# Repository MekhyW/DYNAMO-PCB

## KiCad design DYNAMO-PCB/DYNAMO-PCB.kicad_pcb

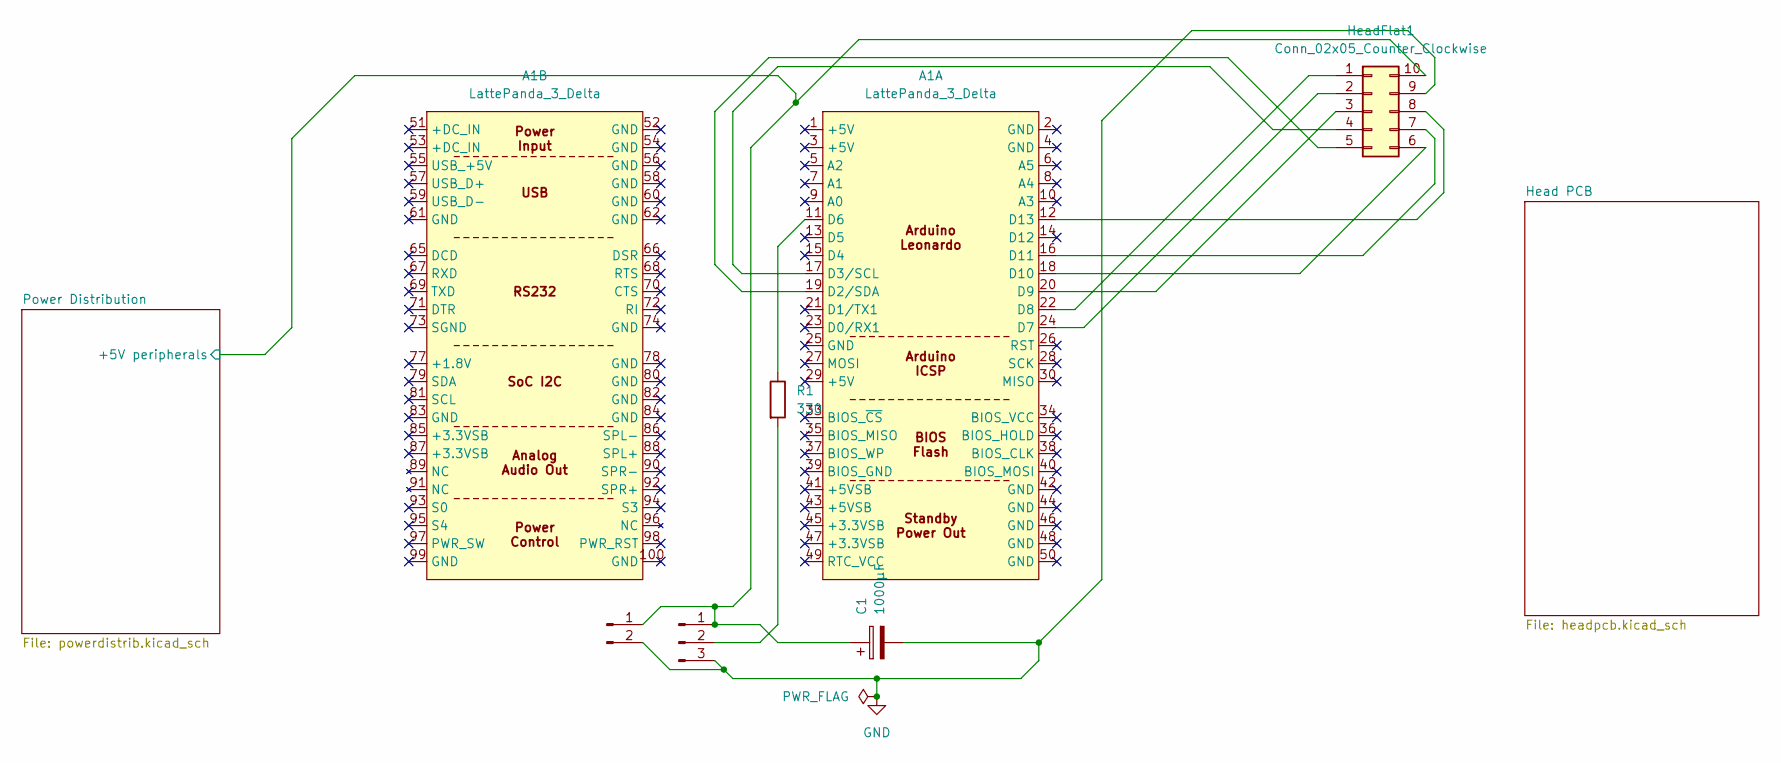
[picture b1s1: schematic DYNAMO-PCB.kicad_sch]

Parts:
A1: LattePanda_3_Delta
C1: 1000µF; CP_Radial_D10.0mm_P5.00mm
CentralFan1: Conn_01x02_Pin; PinHeader_1x02_P2.54mm_Vertical
CentralLEDs1: Conn_01x03_Pin; PinHeader_1x03_P2.54mm_Vertical
HeadFlat1: Conn_02x05_Counter_Clockwise; PinHeader_2x05_P2.54mm_Vertical
R1: 330; R_Axial_DIN0309_L9.0mm_D3.2mm_P12.70mm_Horizontal

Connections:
/Power Distribution/+5V peripherals: C1.1, CentralFan1.1, CentralLEDs1.1, HeadFlat1.10; also elsewhere on the board
GND: C1.2, CentralFan1.2, CentralLEDs1.3, HeadFlat1.9; also elsewhere on the board
unnamed: A1.19 (D2/SDA), HeadFlat1.5
unnamed: A1.17 (D3/SCL), HeadFlat1.4
unnamed: A1.11 (D6), R1.1
unnamed: A1.24 (D7), HeadFlat1.2
unnamed: A1.22 (D8), HeadFlat1.1
unnamed: A1.20 (D9), HeadFlat1.3
unnamed: A1.18 (D10), HeadFlat1.6
unnamed: A1.16 (D11), HeadFlat1.7
unnamed: A1.12 (D13), HeadFlat1.8
unnamed: CentralLEDs1.2, R1.2

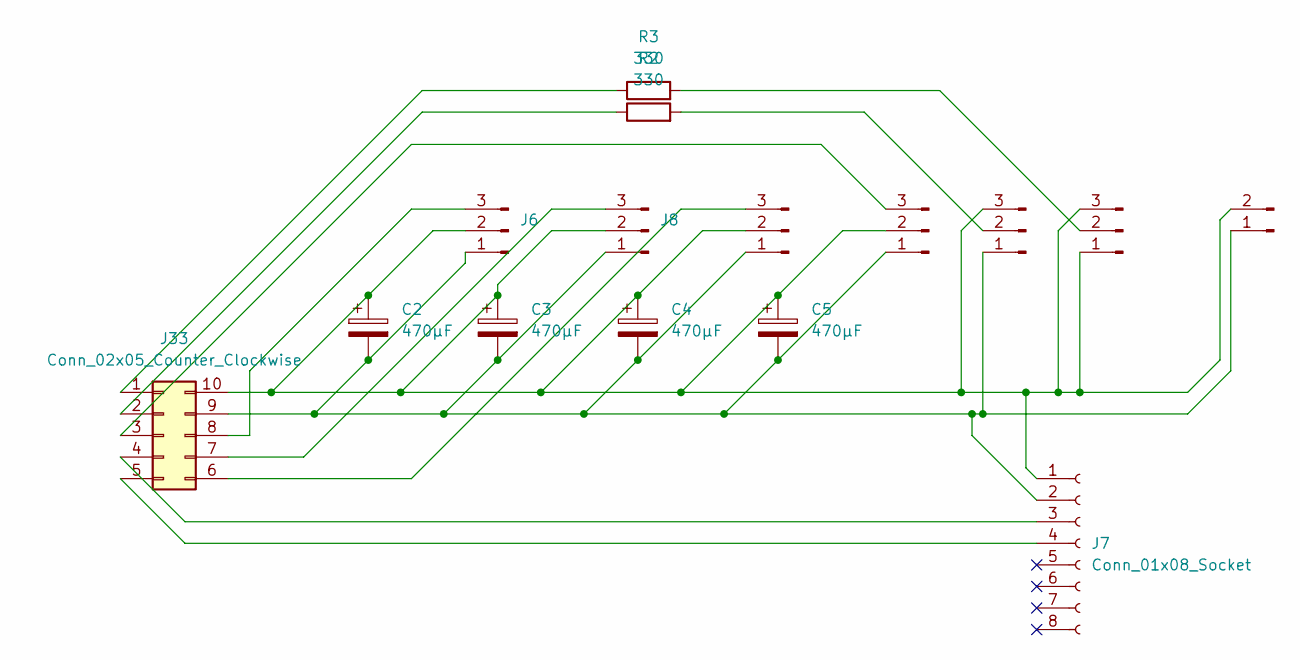
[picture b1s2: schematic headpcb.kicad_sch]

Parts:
C2, C3, C4, C5: 470µF; CP_Radial_D8.0mm_P3.50mm
J5: Conn_01x02_Pin; PinHeader_1x02_P2.54mm_Vertical
J6, J8, J9, J10, J11, J12: Conn_01x03_Pin; PinHeader_1x03_P2.54mm_Vertical
J7: Conn_01x08_Socket; PinSocket_1x08_P2.54mm_Horizontal
J33: Conn_02x05_Counter_Clockwise; PinHeader_2x05_P2.54mm_Vertical
R2, R3: 330; R_Axial_DIN0309_L9.0mm_D3.2mm_P12.70mm_Horizontal

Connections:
unnamed: C2.2, C3.2, C4.2, C5.2, J5.1, J6.1, J7.2, J8.1, J9.1, J10.1, J11.1, J33.9
unnamed: C2.1, C3.1, C4.1, C5.1, J5.2, J6.2, J7.1, J8.2, J9.2, J10.2, J11.3, J12.1, J12.3, J33.10
unnamed: J10.3, J33.3
unnamed: J11.2, R2.2
unnamed: J12.2, R3.2
unnamed: J33.1, R3.1
unnamed: J33.2, R2.1
unnamed: J7.3, J33.4
unnamed: J7.4, J33.5
unnamed: J9.3, J33.6
unnamed: J8.3, J33.7
unnamed: J6.3, J33.8

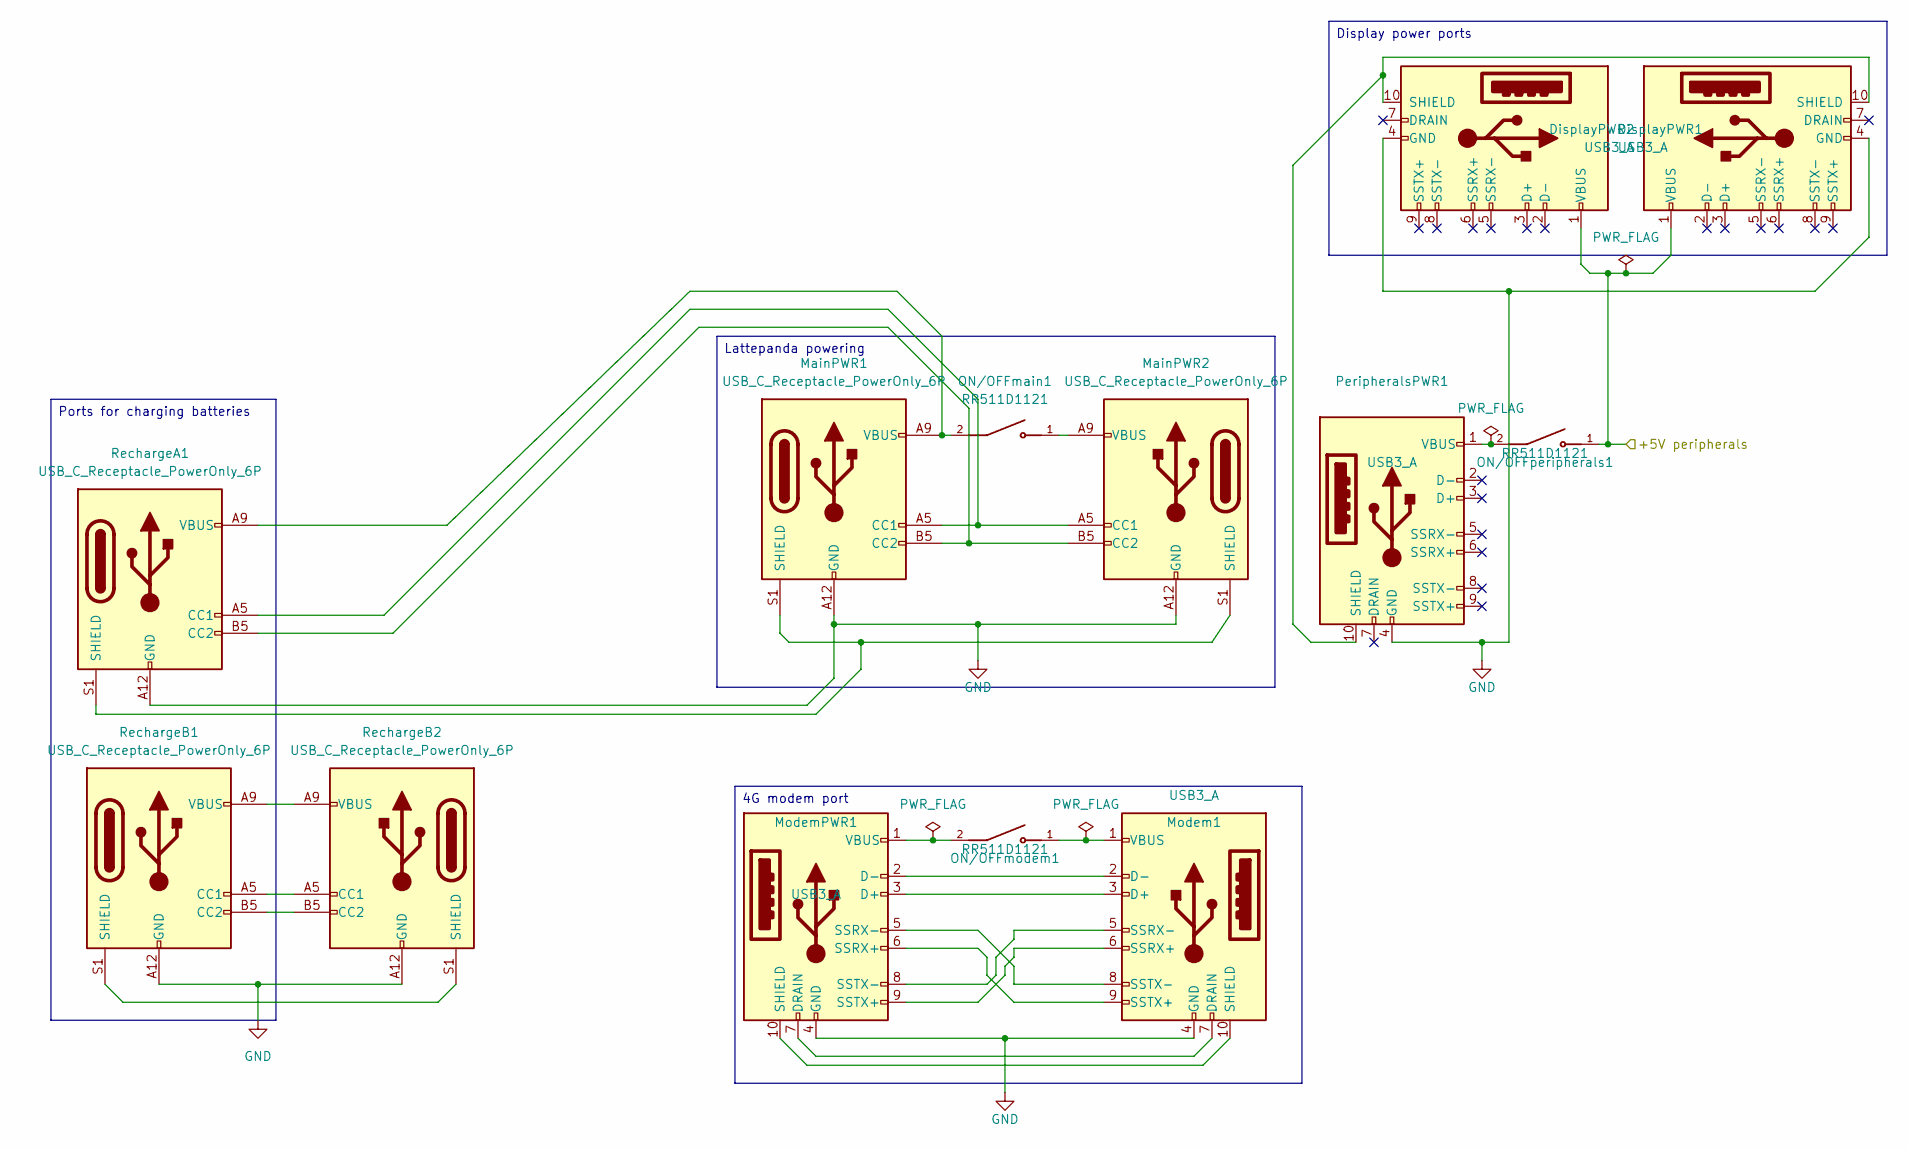
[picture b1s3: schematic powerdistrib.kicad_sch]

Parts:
DisplayPWR1, DisplayPWR2: USB3_A; 692122030100
MainPWR1, MainPWR2: USB_C_Receptacle_PowerOnly_6P; USB_C_Receptacle_GCT_USB4125-xx-x_6P_TopMnt_Horizontal
Modem1: USB3_A; 692122030100
ModemPWR1: USB3_A; 692122030100
ON/OFFmain1: RR511D1121; E-SWITCH_RR511D1121; PARTREV A
ON/OFFmodem1: RR511D1121; E-SWITCH_RR511D1121; PARTREV A
ON/OFFperipherals1: RR511D1121; E-SWITCH_RR511D1121; PARTREV A
PeripheralsPWR1: USB3_A; 692122030100
RechargeA1: USB_C_Receptacle_PowerOnly_6P; USB_C_Receptacle_GCT_USB4125-xx-x_6P_TopMnt_Horizontal
RechargeB1, RechargeB2: USB_C_Receptacle_PowerOnly_6P; USB_C_Receptacle_GCT_USB4125-xx-x_6P_TopMnt_Horizontal

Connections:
/Power Distribution/+5V peripherals: DisplayPWR1.1 (VBUS), DisplayPWR2.1 (VBUS), ON/OFFperipherals1.1; also elsewhere on the board
GND: DisplayPWR1.4 (GND), DisplayPWR2.4 (GND), MainPWR1.A12 (GND), MainPWR1.B12 (GND), MainPWR2.A12 (GND), MainPWR2.B12 (GND), Modem1.4 (GND), ModemPWR1.4 (GND), PeripheralsPWR1.4 (GND), RechargeA1.A12 (GND), RechargeA1.B12 (GND), RechargeB1.A12 (GND), RechargeB1.B12 (GND), RechargeB2.A12 (GND), RechargeB2.B12 (GND); also elsewhere on the board
unnamed: DisplayPWR1.10 (SHIELD), DisplayPWR2.10 (SHIELD), PeripheralsPWR1.10 (SHIELD)
unnamed: MainPWR1.A5 (CC1), MainPWR2.A5 (CC1), RechargeA1.A5 (CC1)
unnamed: MainPWR1.B5 (CC2), MainPWR2.B5 (CC2), RechargeA1.B5 (CC2)
unnamed: MainPWR1.S1 (SHIELD), MainPWR2.S1 (SHIELD), RechargeA1.S1 (SHIELD)
unnamed: MainPWR1.A9 (VBUS), MainPWR1.B9 (VBUS), ON/OFFmain1.2, RechargeA1.A9 (VBUS), RechargeA1.B9 (VBUS)
unnamed: MainPWR2.A9 (VBUS), MainPWR2.B9 (VBUS), ON/OFFmain1.1
unnamed: Modem1.3 (D+), ModemPWR1.3 (D+)
unnamed: Modem1.2 (D-), ModemPWR1.2 (D-)
unnamed: Modem1.7 (DRAIN), ModemPWR1.7 (DRAIN)
unnamed: Modem1.10 (SHIELD), ModemPWR1.10 (SHIELD)
unnamed: Modem1.6 (SSRX+), ModemPWR1.9 (SSTX+)
unnamed: Modem1.5 (SSRX-), ModemPWR1.8 (SSTX-)
unnamed: Modem1.9 (SSTX+), ModemPWR1.6 (SSRX+)
unnamed: Modem1.8 (SSTX-), ModemPWR1.5 (SSRX-)
unnamed: Modem1.1 (VBUS), ON/OFFmodem1.1
unnamed: ModemPWR1.1 (VBUS), ON/OFFmodem1.2
unnamed: ON/OFFperipherals1.2, PeripheralsPWR1.1 (VBUS)
unnamed: RechargeB1.A5 (CC1), RechargeB2.A5 (CC1)
unnamed: RechargeB1.B5 (CC2), RechargeB2.B5 (CC2)
unnamed: RechargeB1.S1 (SHIELD), RechargeB2.S1 (SHIELD)
unnamed: RechargeB1.A9 (VBUS), RechargeB1.B9 (VBUS), RechargeB2.A9 (VBUS), RechargeB2.B9 (VBUS)

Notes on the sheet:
Display power ports
4G modem port
Lattepanda powering
Ports for charging batteries

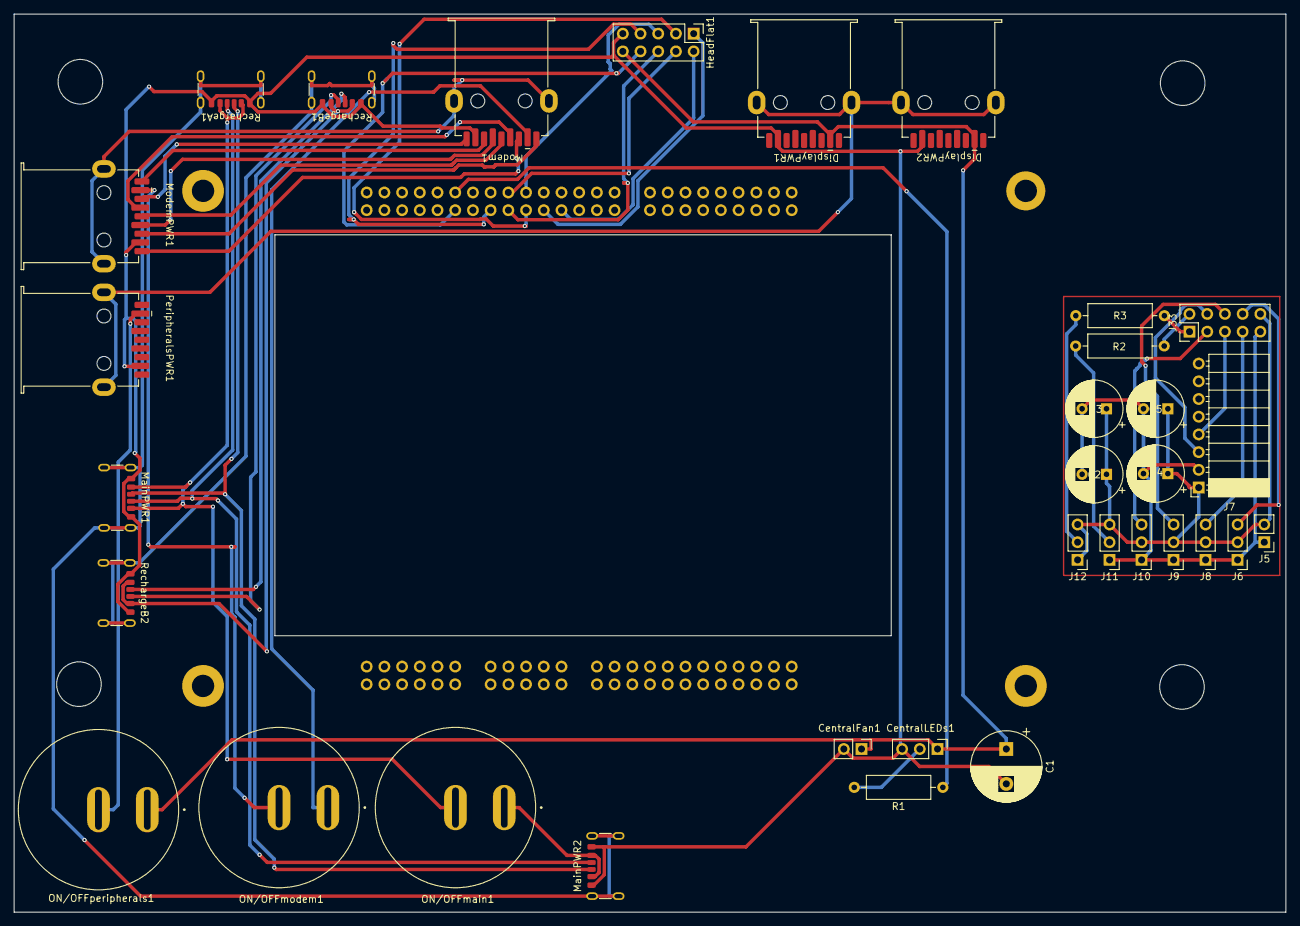
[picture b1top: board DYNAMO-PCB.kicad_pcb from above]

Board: 2 copper layers, 182.4 x 128.8 mm, 34 parts (1 on the bottom side), 45 nets.

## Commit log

2025-05-15 symbols
2025-05-15 on/off switch
2025-05-18 692122030100
2025-05-18 footprint assignments
2025-05-18 schematic wip
2025-05-19 second hdmi port on subsheet
2025-05-19 removed unncessary ic
2025-05-19 removed usb7206
2025-05-20 wired headpcb sch
2025-05-21 schematic complete (pre-ERC)
2025-05-23 fix erc errors
2025-05-27 placement wip
2025-05-27 headphone jack
2025-05-27 routing
2025-06-03 further simplified
2025-06-13 more compact
2025-06-13 track width 0.2 --> 0.5
2025-06-13 Gerber
2025-06-17 Drill files
